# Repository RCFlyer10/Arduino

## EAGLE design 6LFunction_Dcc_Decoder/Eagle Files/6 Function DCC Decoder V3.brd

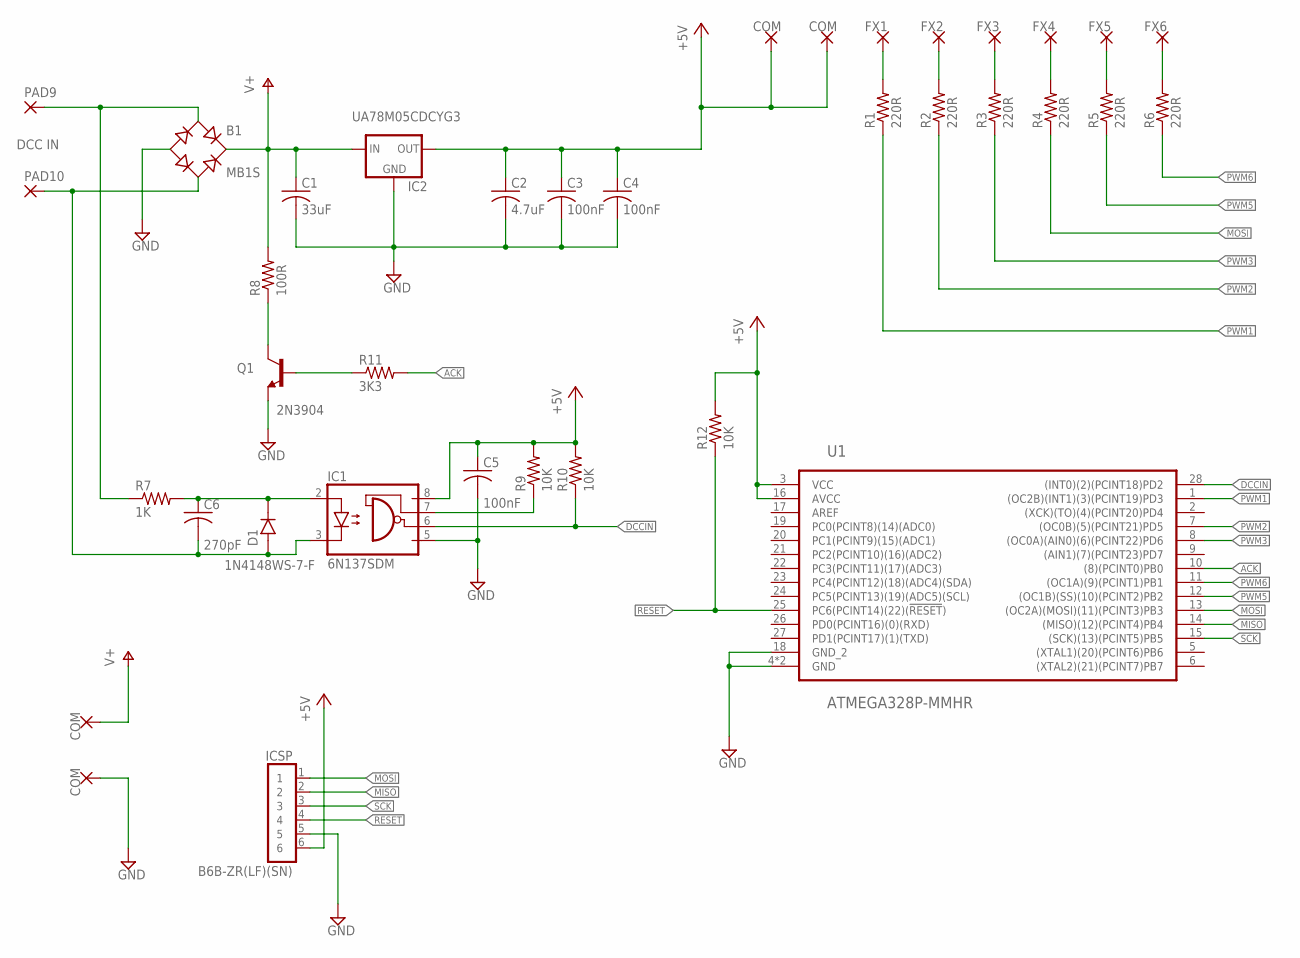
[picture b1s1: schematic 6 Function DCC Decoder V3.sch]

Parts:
B1: MB1S; SOIC-4
C1: 33uF; C1206
C2: 4.7uF; C0603K
C3, C4, C5: 100nF; C0402K
C6: 270pF; C0402K
D1: 1N4148WS-7-F; SOD2513X120N
IC1: 6N137SDM; SOP254P1030X508-8N
IC2: UA78M05CDCYG3; SOT230P700X180-4N
ICSP: B6B-ZR(LF)(SN); JST_B6B-ZR(LF)(SN)
PAD1: FX1; SMD1,27-2,54
PAD2: FX2; SMD1,27-2,54
PAD3: FX3; SMD1,27-2,54
PAD4: FX4; SMD1,27-2,54
PAD5: FX5; SMD1,27-2,54
PAD6: FX6; SMD1,27-2,54
PAD7, PAD8, PAD11, PAD12: COM; SMD1,27-2,54
PAD9, PAD10: SMD2; SMD1,27-2,54
Q1: 2N3904; SOT23
R1, R2, R3, R4, R5, R6: 220R; R0402
R7: 1K; R0402
R8: 100R; R1206
R9, R10, R12: 10K; R0402
R11: 3K3; R0402
U1: ATMEGA328P-MMHR; QFN45P400X400X100-29N

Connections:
+5V: C2.1, C3.1, C4.1, C5.1, IC1.8 (VCC), IC2.3 (OUT), ICSP.6, PAD7.1, PAD8.1, R9.2, R10.2, R12.2, U1.3 (VCC), U1.16 (AVCC)
ACK: R11.2, U1.10 ((8)(PCINT0)PB0)
ACKB: Q1.1 (B), R11.1
DCCA: B1.~1 (AC1), PAD9.1, R7.1
DCCA_: C6.1, D1.C, IC1.2 (A), R7.2
DCCB: B1.~2 (AC2), C6.2, D1.A, IC1.3 (C), PAD10.1
DCCIN: IC1.6 (VO), R10.1, U1.28 ((INT0)(2)(PCINT18)PD2)
GND: B1.-, C1.2, C2.2, C3.2, C4.2, C5.2, IC1.5 (GND), IC2.2 (GND), IC2.4 (GND), ICSP.5, PAD12.1, Q1.2 (E), U1.4 (GND), U1.18 (GND_2), U1.29 (GND)
MISO: ICSP.2, U1.14 ((MISO)(12)(PCINT4)PB4)
MOSI: ICSP.1, R4.1, U1.13 ((OC2A)(MOSI)(11)(PCINT3)PB3)
unnamed: PAD1.1, R1.2
unnamed: PAD2.1, R2.2
unnamed: PAD3.1, R3.2
unnamed: PAD4.1, R4.2
unnamed: PAD5.1, R5.2
unnamed: PAD6.1, R6.2
unnamed: IC1.7 (VE), R9.1
unnamed: Q1.3 (C), R8.1
PWM1: R1.1, U1.1 ((OC2B)(INT1)(3)(PCINT19)PD3)
PWM2: R2.1, U1.7 ((OC0B)(5)(PCINT21)PD5)
PWM3: R3.1, U1.8 ((OC0A)(AIN0)(6)(PCINT22)PD6)
PWM5: R5.1, U1.12 ((OC1B)(SS)(10)(PCINT2)PB2)
PWM6: R6.1, U1.11 ((OC1A)(9)(PCINT1)PB1)
RESET: ICSP.4, R12.1, U1.25 (PC6(PCINT14)(22)(!RESET!))
SCK: ICSP.3, U1.15 ((SCK)(13)(PCINT5)PB5)
V+: B1.+, C1.1, IC2.1 (IN), PAD11.1, R8.2

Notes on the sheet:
DCC IN

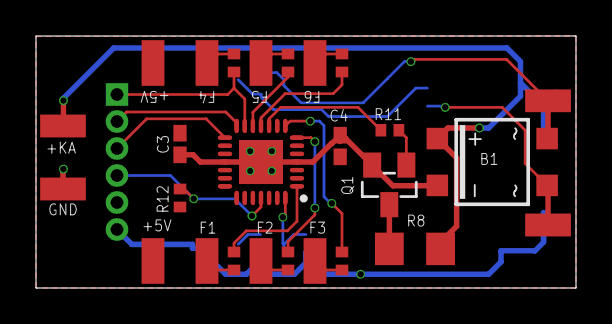
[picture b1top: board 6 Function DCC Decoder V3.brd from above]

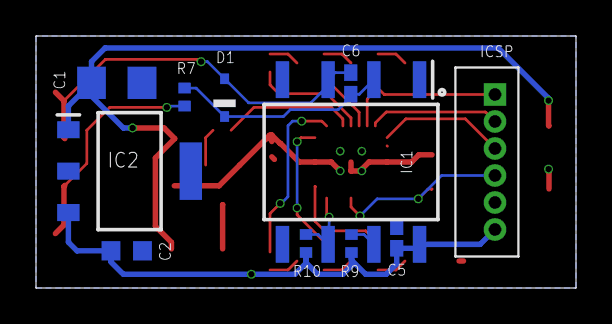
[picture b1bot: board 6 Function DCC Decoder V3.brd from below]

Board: 2 copper layers, 30.0 x 14.0 mm, 37 parts (11 on the bottom side), 26 nets.

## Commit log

2024-02-04 Initial
2024-02-05 Updated JMRI decoder definition
2024-02-05 Added Product Id CVs
2024-02-05 Added Eagle Files
2024-02-10 Initial
    Initial
2024-02-18 Version 2.1
    Initial
2024-02-18 Remove
    LocoPwmV2.0
2024-03-07 6LFunction DCC Decoder
    Added Flicker Effect
2024-03-07 6L Function DCC Decoder
    Refactor
2024-04-01 6LFunction_Dcc_Decoder
    Minor Changes
2024-08-05 Minor
    Minor Changes
2024-08-07 1.0.0
2024-09-01 Final
